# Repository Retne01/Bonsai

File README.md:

# Bonsai
This is a completely through hole 75% take on the TGR Alice layout.

If you want to put one together for yourself you can follow the guide for the FR4 sandwich style pictured above you can follow [the guide here](./Guides/FR4/)  If you would prefer to make an acrylic style case as pictured below you can follow [the guide here](./Guides/Acrylic/).

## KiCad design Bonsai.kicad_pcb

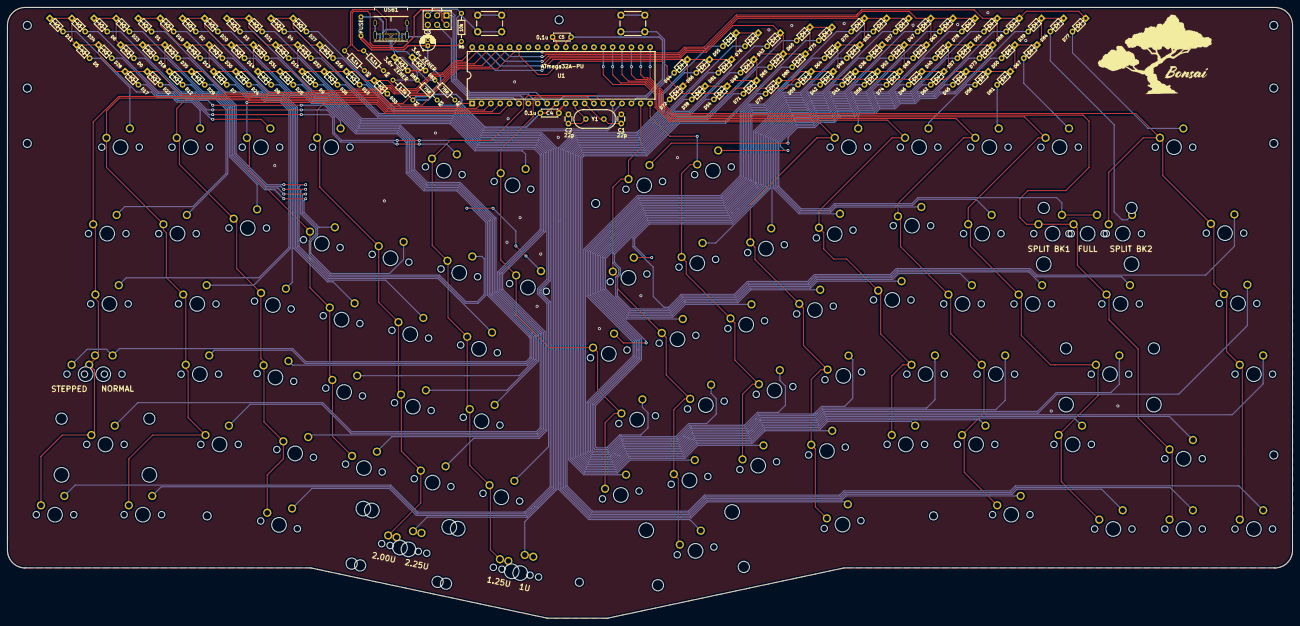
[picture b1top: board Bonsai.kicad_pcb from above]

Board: 2 copper layers, 348.5 x 165.6 mm, 203 parts (0 on the bottom side), 120 nets.

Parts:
BOOT1: BOOT; SW_PUSH_6mm
C1, C2: 22p; C_Disc_D3.0mm_W1.6mm_P2.50mm
C3: 4.7u; CP_Radial_D4.0mm_P1.50mm
C4, C5: 0.1u; C_Disc_D4.3mm_W1.9mm_P5.00mm
D0, D1, D2, D3, D4, D5, D6, D7, D8, D9, D10, D11, D12, D13, D14, D15, D16, D17, D18, D19, D20, D21, D22, D23, D24, D25, D26, D27, D28, D29, D30, D31, D32, D33, D34, D35, D36, D37, D38, D39, D40, D41, D42, D43, D44, D45, D46, D47, D48, D49, D50, D51, D52, D53, D54, D55, D56, D57, D58, D59, D60, D61, D62, D63, D64, D65, D66, D67, D68, D69, D70, D71, D72, D73, D74, D75, D76, D77, D78, D79, D80, D81, D84: D; D_DO-35_SOD27_P5.08mm_Horizontal
D82, D83: 3.6v; D_DO-35_SOD27_P5.08mm_Horizontal
F1: 500mA; polyfuse_5.1mm
G01: LOGO; Bonsai Front Badge 6k x6k
H1, H2, H3, H4, H5, H6, H7, H8, H9, H10, H11, H12: MountingHole; MountingHole_2.2mm_M2
J1: AVR-ISP-6; AVR_ICSP_3x2
R1: 1.5k; R_Axial_DIN0204_L3.6mm_D1.6mm_P7.62mm_Horizontal
R2, R3: 75R; R_Axial_DIN0204_L3.6mm_D1.6mm_P7.62mm_Horizontal
R4, R5: 5.1k; R_Axial_DIN0204_L3.6mm_D1.6mm_P7.62mm_Horizontal
R6: 10k; R_Axial_DIN0204_L3.6mm_D1.6mm_P7.62mm_Horizontal
RESET1: RESET; SW_PUSH_6mm
SW_1, SW_2, SW_3, SW_4, SW_5, SW_6, SW_7, SW_8, SW_9, SW_10: SW_Push; MXOnly-1U-NoLED
SW_A1: SW_Push; MXOnly-1U-NoLED
SW_APST1: SW_Push; MXOnly-1U-NoLED
SW_BKSP1: SW_Push; MXOnly-2U-NoLED
SW_BKSP11, SW_BKSP12: SW_Push; MXOnly-1U-NoLED
SW_B_LEFT1: SW_Push; MXOnly-1U-NoLED
SW_B_RIGHT1: SW_Push; MXOnly-1U-NoLED
SW_C1: SW_Push; MXOnly-1U-NoLED
SW_COMMA1: SW_Push; MXOnly-1U-NoLED
SW_CPLK1: SW_Push; MXOnly-1.75U-NoLED
SW_CPLKSTPD1: SW_Push; MXOnly-1.25U-NoLED
SW_D1: SW_Push; MXOnly-1U-NoLED
SW_DASH1: SW_Push; MXOnly-1U-NoLED
SW_DOWN1: SW_Push; MXOnly-1U-NoLED
SW_E1: SW_Push; MXOnly-1U-NoLED
SW_ENT1: SW_Push; MXOnly-2.25U-NoLED
SW_ESC1: SW_Push; MXOnly-1U-NoLED
SW_F1, SW_F2, SW_F3, SW_F4, SW_F5, SW_F6, SW_F7, SW_F8, SW_F9, SW_F10, SW_F11, SW_F12, SW_F13: SW_Push; MXOnly-1U-NoLED
SW_FN1: SW_Push; MXOnly-1U-NoLED
SW_FN2: SW_Push; MXOnly-1.25U-NoLED
SW_G1: SW_Push; MXOnly-1U-NoLED
SW_H1: SW_Push; MXOnly-1U-NoLED
SW_I1: SW_Push; MXOnly-1U-NoLED
SW_J1: SW_Push; MXOnly-1U-NoLED
SW_K1: SW_Push; MXOnly-1U-NoLED
SW_L1: SW_Push; MXOnly-1U-NoLED
SW_LALT1: SW_Push; MXOnly-1.5U-NoLED
SW_LCTRL1: SW_Push; MXOnly-1.25U-NoLED
SW_LEFT1: SW_Push; MXOnly-1U-NoLED
SW_LSHFT1: SW_Push; MXOnly-2.25U-NoLED
SW_LSPC1: SW_Push; MXOnly-2.25U-ReversedStabilizers-NoLED
SW_LSPC2: SW_Push; MXOnly-2U-ReversedStabilizers-NoLED
SW_M1, SW_M2, SW_M3, SW_M4, SW_M5: SW_Push; MXOnly-1U-NoLED
SW_N1: SW_Push; MXOnly-1U-NoLED
SW_O1: SW_Push; MXOnly-1U-NoLED
SW_P1: SW_Push; MXOnly-1U-NoLED
SW_PLUS1: SW_Push; MXOnly-1U-NoLED
SW_PRD1: SW_Push; MXOnly-1U-NoLED
SW_Q1: SW_Push; MXOnly-1U-NoLED
SW_R1: SW_Push; MXOnly-1U-NoLED
SW_RALT1: SW_Push; MXOnly-1.5U-NoLED
SW_RCTRL1: SW_Push; MXOnly-1.25U-NoLED
SW_RGHT1: SW_Push; MXOnly-1U-NoLED
SW_RSHFT1: SW_Push; MXOnly-1.75U-NoLED
SW_RSPC1: SW_Push; MXOnly-2.75U-ReversedStabilizers-NoLED
SW_S1: SW_Push; MXOnly-1U-NoLED
SW_SCLN1: SW_Push; MXOnly-1U-NoLED
SW_SLSH1: SW_Push; MXOnly-1U-NoLED
SW_T1: SW_Push; MXOnly-1U-NoLED
SW_TAB1: SW_Push; MXOnly-1.5U-NoLED
SW_U1: SW_Push; MXOnly-1U-NoLED
SW_UP1: SW_Push; MXOnly-1U-NoLED
SW_V1: SW_Push; MXOnly-1U-NoLED
SW_W1: SW_Push; MXOnly-1U-NoLED
SW_WIN1: SW_Push; MXOnly-1.25U-NoLED
SW_X1: SW_Push; MXOnly-1U-NoLED
SW_Y1: SW_Push; MXOnly-1U-NoLED
SW_Z1: SW_Push; MXOnly-1U-NoLED
SW_[1: SW_Push; MXOnly-1U-NoLED
SW_]1: SW_Push; MXOnly-1U-NoLED
SW_|1: SW_Push; MXOnly-1.5U-NoLED
U1: ATmega32A-PU; DIP-40_W15.24mm
USB1: USB_C_Receptacle_USB2.0; USB_C_GCT_USB4085
Y1: Crystal; Crystal_HC49-4H_Vertical

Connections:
+5V: C3.1, C4.1, C5.1, F1.1, J1.2, R1.1, R6.1, U1.10, U1.30
D+: R2.1, U1.16
D-: R3.1, U1.17
GND: BOOT1.1, C1.2, C2.2, C3.2, C4.2, C5.2, D82.2, D83.2, J1.6, R4.1, R5.1, RESET1.1, U1.11, U1.31, USB1.A1, USB1.A12, USB1.B1, USB1.B12, USB1.S1
MISO: J1.1, U1.7
MOSI: J1.4, U1.6
unnamed: C1.1, U1.13, Y1.1
unnamed: C2.1, U1.12, Y1.2
unnamed: D0.2, SW_ESC1.2
unnamed: D1.2, SW_TAB1.2
unnamed: D2.2, SW_CPLK1.2, SW_CPLKSTPD1.1
unnamed: D3.2, SW_LSHFT1.2
unnamed: D4.2, SW_LCTRL1.2
unnamed: D5.2, SW_F1.2
unnamed: D6.2, SW_1.2
unnamed: D7.2, SW_Q1.2
unnamed: D8.2, SW_A1.2
unnamed: D9.2, SW_Z1.2
unnamed: D10.2, SW_WIN1.2
unnamed: D11.2, SW_F2.2
unnamed: D12.2, SW_2.2
unnamed: D13.2, SW_W1.2
unnamed: D14.2, SW_S1.2
unnamed: D15.2, SW_X1.2
unnamed: D16.2, SW_LALT1.2
unnamed: D17.2, SW_F3.2
unnamed: D18.2, SW_3.2
unnamed: D19.2, SW_E1.2
unnamed: D20.2, SW_D1.2
unnamed: D21.2, SW_C1.2
unnamed: D22.2, SW_F4.2
unnamed: D23.2, SW_4.2
unnamed: D24.2, SW_R1.2
unnamed: D25.2, SW_F13.2
unnamed: D26.2, SW_V1.2
unnamed: D27.2, SW_LSPC1.2, SW_LSPC2.2
unnamed: D28.2, SW_F5.2
unnamed: D29.2, SW_5.2
unnamed: D30.2, SW_T1.2
unnamed: D31.2, SW_G1.2
unnamed: D32.2, SW_B_LEFT1.2
unnamed: D33.2, SW_FN1.2, SW_FN2.2
unnamed: D34.2, SW_F6.2
unnamed: D35.2, SW_6.2
unnamed: D36.2, SW_Y1.2
unnamed: D37.2, SW_H1.2
unnamed: D38.2, SW_B_RIGHT1.2
unnamed: D39.2, SW_F7.2
unnamed: D40.2, SW_7.2
unnamed: D41.2, SW_U1.2
unnamed: D42.2, SW_J1.2
unnamed: D43.2, SW_N1.2
unnamed: D44.2, SW_RSPC1.2
unnamed: D45.2, SW_F8.2
unnamed: D46.2, SW_8.2
unnamed: D47.2, SW_I1.2
unnamed: D48.2, SW_K1.2
unnamed: D49.2, SW_M5.2
unnamed: D50.2, SW_F9.2
unnamed: D51.2, SW_9.2
unnamed: D52.2, SW_O1.2
unnamed: D53.2, SW_L1.2
unnamed: D54.2, SW_COMMA1.2
unnamed: D55.2, SW_RALT1.2
unnamed: D56.2, SW_F10.2
unnamed: D57.2, SW_10.2
unnamed: D58.2, SW_P1.2
unnamed: D59.2, SW_SCLN1.2
unnamed: D60.2, SW_PRD1.2
unnamed: D61.2, SW_F11.2
unnamed: D62.2, SW_DASH1.2
unnamed: D63.2, SW_[1.2
unnamed: D64.2, SW_APST1.2
unnamed: D65.2, SW_SLSH1.2
unnamed: D66.2, SW_RCTRL1.2
unnamed: D67.2, SW_F12.2
unnamed: D68.2, SW_PLUS1.2
unnamed: D69.2, SW_]1.2
unnamed: D70.2, SW_ENT1.2
unnamed: D71.2, SW_RSHFT1.2
unnamed: D72.2, SW_LEFT1.2
unnamed: D73.2, SW_BKSP1.2, SW_BKSP11.2
unnamed: D74.2, SW_|1.2
unnamed: D75.2, SW_UP1.2
unnamed: D76.2, SW_DOWN1.2
unnamed: D77.2, SW_M1.2
unnamed: D78.2, SW_M2.2
unnamed: D79.2, SW_M3.2
unnamed: D80.2, SW_M4.2
unnamed: D81.2, SW_RGHT1.2
unnamed: D82.1, R2.2, USB1.A6, USB1.B6
unnamed: D83.1, R1.2, R3.2, USB1.A7, USB1.B7
unnamed: D84.2, SW_BKSP12.2
unnamed: R4.2, USB1.A5
unnamed: R5.2, USB1.B5
SCK: J1.3, U1.8
VCC: F1.2, USB1.A4, USB1.A9, USB1.B4, USB1.B9
boot: BOOT1.2, U1.18
col0: SW_CPLK1.1, SW_CPLKSTPD1.2, SW_ESC1.1, SW_LCTRL1.1, SW_LSHFT1.1, SW_TAB1.1, U1.1
col1: SW_1.1, SW_A1.1, SW_F1.1, SW_Q1.1, SW_WIN1.1, SW_Z1.1, U1.2
col2: SW_2.1, SW_F2.1, SW_LALT1.1, SW_S1.1, SW_W1.1, SW_X1.1, U1.3
col3: SW_3.1, SW_C1.1, SW_D1.1, SW_E1.1, SW_F3.1, U1.4
col4: SW_4.1, SW_F4.1, SW_F13.1, SW_LSPC1.1, SW_LSPC2.1, SW_R1.1, SW_V1.1, U1.5
col5: SW_5.1, SW_B_LEFT1.1, SW_F5.1, SW_FN1.1, SW_FN2.1, SW_G1.1, SW_T1.1, U1.15
col6: SW_6.1, SW_B_RIGHT1.1, SW_F6.1, SW_H1.1, SW_Y1.1, U1.14
col7: SW_7.1, SW_F7.1, SW_J1.1, SW_N1.1, SW_RSPC1.1, SW_U1.1, U1.19
col8: SW_8.1, SW_F8.1, SW_I1.1, SW_K1.1, SW_M5.1, U1.20
col9: SW_9.1, SW_COMMA1.1, SW_F9.1, SW_L1.1, SW_O1.1, SW_RALT1.1, U1.26
col10: SW_10.1, SW_F10.1, SW_P1.1, SW_PRD1.1, SW_SCLN1.1, U1.25
col11: SW_APST1.1, SW_DASH1.1, SW_F11.1, SW_RCTRL1.1, SW_SLSH1.1, SW_[1.1, U1.24
col12: SW_ENT1.1, SW_F12.1, SW_LEFT1.1, SW_PLUS1.1, SW_RSHFT1.1, SW_]1.1, U1.23
col13: SW_BKSP1.1, SW_BKSP11.1, SW_DOWN1.1, SW_UP1.1, SW_|1.1, U1.22
col14: SW_BKSP12.1, SW_M1.1, SW_M2.1, SW_M3.1, SW_M4.1, SW_RGHT1.1, U1.21
reset: J1.5, R6.2, RESET1.2, U1.9
row0: D5.1, D11.1, D17.1, D22.1, D28.1, D34.1, D39.1, D45.1, D50.1, D56.1, D61.1, D67.1, D84.1, U1.35
row1: D0.1, D6.1, D12.1, D18.1, D23.1, D29.1, D35.1, D40.1, D46.1, D51.1, D57.1, D62.1, D68.1, D73.1, D77.1, U1.36
row2: D1.1, D7.1, D13.1, D19.1, D24.1, D30.1, D36.1, D41.1, D47.1, D52.1, D58.1, D63.1, D69.1, D74.1, D78.1, U1.37
row3: D2.1, D8.1, D14.1, D20.1, D25.1, D31.1, D37.1, D42.1, D48.1, D53.1, D59.1, D64.1, D70.1, D79.1, U1.38
row4: D3.1, D9.1, D15.1, D21.1, D26.1, D32.1, D38.1, D43.1, D49.1, D54.1, D60.1, D65.1, D71.1, D75.1, D80.1, U1.39
row5: D4.1, D10.1, D16.1, D27.1, D33.1, D44.1, D55.1, D66.1, D72.1, D76.1, D81.1, U1.40

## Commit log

2020-07-14 Plate files
    An attempt at making an FR4 plate in KiCad.
2020-07-14 Fixed missing VCC trace
2020-07-15 Fixed a missing trace.
2020-07-15 Fixed some via too close errors
2020-07-16 Working on the plate and potentially a stacked acrylic case.
2020-07-19 Leveled out the bottom of the pcb.
2020-07-19 Fixed the plate to match the pcb adjustment and cleaned up some of the double lines.
2020-07-21 Cleared some space around the backspace stab holes.
2020-07-26 Fixed plate, added art to the PCB and made a base plate with art.
2020-07-26 Set theme jekyll-theme-midnight
2020-07-26 Generated gerbers.
2020-07-30 Removed the hole labels from the silk screen.
2020-09-20 Cleaned up folders and files
2020-09-21 Did some more cleaning of the file structure.
2020-09-21 Updated the Readme
2020-10-12 Cleaned up a little and added a case
2020-10-12 Added README.md to the Case folder
2020-10-12 Changed folder name
2020-11-07 Updated the case Readme and added some pictures.
2020-11-07 Fixed Readme
2020-11-07 Removed spaces from image names
2020-11-22 Removed VIA support
    I've removed the VIA keymap because it was not working properly and there is some functionality that doesn't work properly in VIA with ATmega32A chips. I will add it back once I've had time to figure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
2020-11-22 Added a guide for assembly
    I've added a guide for either the FR4 style board or the Acrylic style board.
2020-11-22 Fixed picture issue in the guide.
2020-11-22 Added pictures of the acrylic case to the homepage.
2020-11-22 Minor formatting
2020-11-23 Updated the guides
